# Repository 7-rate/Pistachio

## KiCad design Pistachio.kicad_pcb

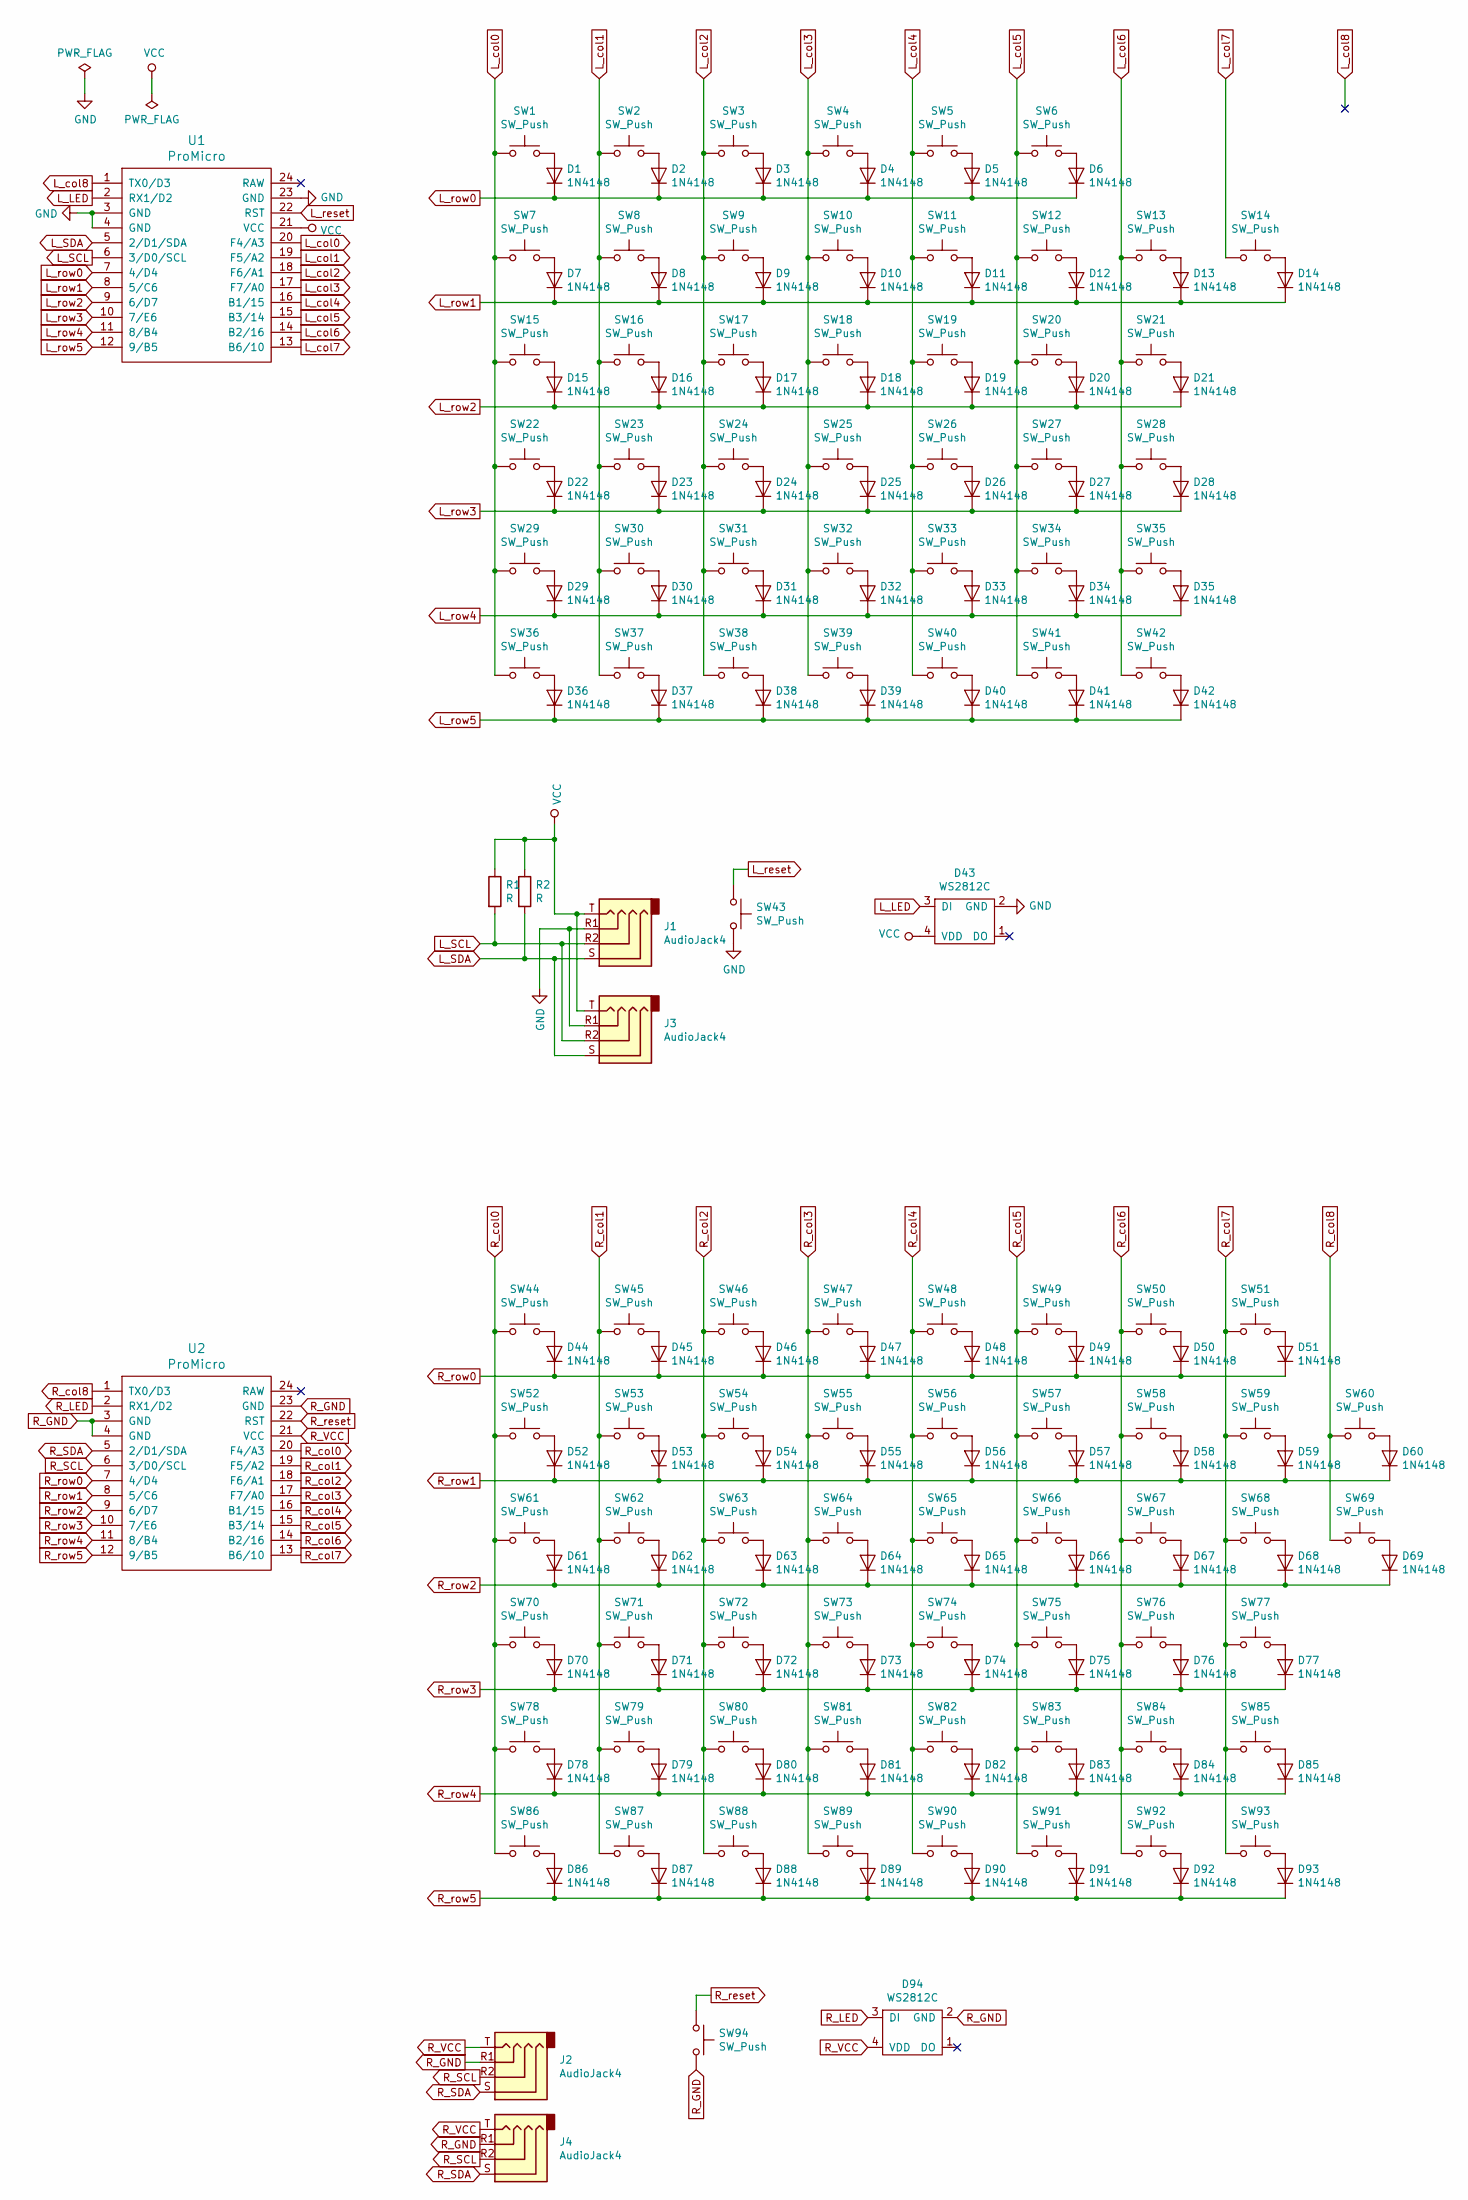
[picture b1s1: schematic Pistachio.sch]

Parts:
D1, D2, D3, D4, D5, D6, D7, D8, D9, D10, D11, D12, D13, D14, D15, D16, D17, D18, D19, D20, D21, D22, D23, D24, D25, D26, D27, D28, D29, D30, D31, D32, D33, D34, D35, D36, D37, D38, D39, D40, D41, D42, D44, D45, D46, D47, D48, D49, D50, D51, D52, D53, D54, D55, D56, D57, D58, D59, D60, D61, D62, D63, D64, D65, D66, D67, D68, D69, D70, D71, D72, D73, D74, D75, D76, D77, D78, D79, D80, D81, D82, D83, D84, D85, D86, D87, D88, D89, D90, D91, D92, D93: 1N4148; D3_SMD_v2
D43, D94: WS2812C; WS2812C-2020
J1, J2, J3, J4: AudioJack4; MJ-4PP-9_1side
R1, R2: R; R_0603_1608Metric_Pad1.05x0.95mm_HandSolder
SW1, SW2, SW3, SW4, SW5, SW6, SW7, SW8, SW9, SW10, SW11, SW12, SW13, SW14, SW15, SW16, SW17, SW18, SW19, SW20, SW21, SW22, SW23, SW24, SW25, SW26, SW27, SW28, SW29, SW30, SW31, SW32, SW33, SW34, SW35, SW36, SW37, SW38, SW39, SW40, SW41, SW42, SW44, SW45, SW46, SW47, SW48, SW49, SW50, SW51, SW52, SW53, SW54, SW55, SW56, SW57, SW58, SW59, SW60, SW61, SW62, SW63, SW64, SW65, SW66, SW67, SW68, SW69, SW70, SW71, SW72, SW73, SW74, SW75, SW76, SW77, SW78, SW79, SW80, SW81, SW82, SW83, SW84, SW85, SW86, SW87, SW88, SW89, SW90, SW91, SW92, SW93: SW_Push; Kailh_socket_MX_optional
SW43, SW94: SW_Push; ResetSW_1side
U1, U2: ProMicro; ProMicro_v3.5

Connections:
GND: D43.2 (GND), J1.R1, J3.R1, SW43.2, U1.3 (GND), U1.4 (GND), U1.23 (GND)
L_LED: D43.3 (DI), U1.2 (RX1/D2)
L_SCL: J1.R2, J3.R2, R1.2, U1.6 (3/D0/SCL)
L_SDA: J1.S, J3.S, R2.2, U1.5 (2/D1/SDA)
L_col0: SW1.1, SW7.1, SW15.1, SW22.1, SW29.1, SW36.1, U1.20 (F4/A3)
L_col1: SW2.1, SW8.1, SW16.1, SW23.1, SW30.1, SW37.1, U1.19 (F5/A2)
L_col2: SW3.1, SW9.1, SW17.1, SW24.1, SW31.1, SW38.1, U1.18 (F6/A1)
L_col3: SW4.1, SW10.1, SW18.1, SW25.1, SW32.1, SW39.1, U1.17 (F7/A0)
L_col4: SW5.1, SW11.1, SW19.1, SW26.1, SW33.1, SW40.1, U1.16 (B1/15)
L_col5: SW6.1, SW12.1, SW20.1, SW27.1, SW34.1, SW41.1, U1.15 (B3/14)
L_col6: SW13.1, SW21.1, SW28.1, SW35.1, SW42.1, U1.14 (B2/16)
L_col7: SW14.1, U1.13 (B6/10)
L_col8: U1.1 (TX0/D3)
L_reset: SW43.1, U1.22 (RST)
L_row0: D1.1 (K), D2.1 (K), D3.1 (K), D4.1 (K), D5.1 (K), D6.1 (K), U1.7 (4/D4)
L_row1: D7.1 (K), D8.1 (K), D9.1 (K), D10.1 (K), D11.1 (K), D12.1 (K), D13.1 (K), D14.1 (K), U1.8 (5/C6)
L_row2: D15.1 (K), D16.1 (K), D17.1 (K), D18.1 (K), D19.1 (K), D20.1 (K), D21.1 (K), U1.9 (6/D7)
L_row3: D22.1 (K), D23.1 (K), D24.1 (K), D25.1 (K), D26.1 (K), D27.1 (K), D28.1 (K), U1.10 (7/E6)
L_row4: D29.1 (K), D30.1 (K), D31.1 (K), D32.1 (K), D33.1 (K), D34.1 (K), D35.1 (K), U1.11 (8/B4)
L_row5: D36.1 (K), D37.1 (K), D38.1 (K), D39.1 (K), D40.1 (K), D41.1 (K), D42.1 (K), U1.12 (9/B5)
unnamed: D1.2 (A), SW1.2
unnamed: D2.2 (A), SW2.2
unnamed: D3.2 (A), SW3.2
unnamed: D4.2 (A), SW4.2
unnamed: D5.2 (A), SW5.2
unnamed: D6.2 (A), SW6.2
unnamed: D7.2 (A), SW7.2
unnamed: D8.2 (A), SW8.2
unnamed: D9.2 (A), SW9.2
unnamed: D10.2 (A), SW10.2
unnamed: D11.2 (A), SW11.2
unnamed: D12.2 (A), SW12.2
unnamed: D13.2 (A), SW13.2
unnamed: D14.2 (A), SW14.2
unnamed: D15.2 (A), SW15.2
unnamed: D16.2 (A), SW16.2
unnamed: D17.2 (A), SW17.2
unnamed: D18.2 (A), SW18.2
unnamed: D19.2 (A), SW19.2
unnamed: D20.2 (A), SW20.2
unnamed: D21.2 (A), SW21.2
unnamed: D22.2 (A), SW22.2
unnamed: D23.2 (A), SW23.2
unnamed: D24.2 (A), SW24.2
unnamed: D25.2 (A), SW25.2
unnamed: D26.2 (A), SW26.2
unnamed: D27.2 (A), SW27.2
unnamed: D28.2 (A), SW28.2
unnamed: D29.2 (A), SW29.2
unnamed: D30.2 (A), SW30.2
unnamed: D31.2 (A), SW31.2
unnamed: D32.2 (A), SW32.2
unnamed: D33.2 (A), SW33.2
unnamed: D34.2 (A), SW34.2
unnamed: D35.2 (A), SW35.2
unnamed: D36.2 (A), SW36.2
unnamed: D37.2 (A), SW37.2
unnamed: D38.2 (A), SW38.2
unnamed: D39.2 (A), SW39.2
unnamed: D40.2 (A), SW40.2
unnamed: D41.2 (A), SW41.2
unnamed: D42.2 (A), SW42.2
unnamed: D44.2 (A), SW44.2
unnamed: D45.2 (A), SW45.2
unnamed: D46.2 (A), SW46.2
unnamed: D47.2 (A), SW47.2
unnamed: D48.2 (A), SW48.2
unnamed: D49.2 (A), SW49.2
unnamed: D50.2 (A), SW50.2
unnamed: D51.2 (A), SW51.2
unnamed: D52.2 (A), SW52.2
unnamed: D53.2 (A), SW53.2
unnamed: D54.2 (A), SW54.2
unnamed: D55.2 (A), SW55.2
unnamed: D56.2 (A), SW56.2
unnamed: D57.2 (A), SW57.2
unnamed: D58.2 (A), SW58.2
unnamed: D59.2 (A), SW59.2
unnamed: D60.2 (A), SW60.2
unnamed: D61.2 (A), SW61.2
unnamed: D62.2 (A), SW62.2
unnamed: D63.2 (A), SW63.2
unnamed: D64.2 (A), SW64.2
unnamed: D65.2 (A), SW65.2
unnamed: D66.2 (A), SW66.2
unnamed: D67.2 (A), SW67.2
unnamed: D68.2 (A), SW68.2
unnamed: D69.2 (A), SW69.2
unnamed: D70.2 (A), SW70.2
unnamed: D71.2 (A), SW71.2
unnamed: D72.2 (A), SW72.2
unnamed: D73.2 (A), SW73.2
unnamed: D74.2 (A), SW74.2
unnamed: D75.2 (A), SW75.2
unnamed: D76.2 (A), SW76.2
unnamed: D77.2 (A), SW77.2
unnamed: D78.2 (A), SW78.2
unnamed: D79.2 (A), SW79.2
unnamed: D80.2 (A), SW80.2
unnamed: D81.2 (A), SW81.2
unnamed: D82.2 (A), SW82.2
unnamed: D83.2 (A), SW83.2
unnamed: D84.2 (A), SW84.2
unnamed: D85.2 (A), SW85.2
unnamed: D86.2 (A), SW86.2
unnamed: D87.2 (A), SW87.2
unnamed: D88.2 (A), SW88.2
unnamed: D89.2 (A), SW89.2
unnamed: D90.2 (A), SW90.2
unnamed: D91.2 (A), SW91.2
unnamed: D92.2 (A), SW92.2
unnamed: D93.2 (A), SW93.2
R_GND: D94.2 (GND), J2.R1, J4.R1, SW94.2, U2.3 (GND), U2.4 (GND), U2.23 (GND)
R_LED: D94.3 (DI), U2.2 (RX1/D2)
R_SCL: J2.R2, J4.R2, U2.6 (3/D0/SCL)
R_SDA: J2.S, J4.S, U2.5 (2/D1/SDA)
R_VCC: D94.4 (VDD), J2.T, J4.T, U2.21 (VCC)
R_col0: SW44.1, SW52.1, SW61.1, SW70.1, SW78.1, SW86.1, U2.20 (F4/A3)
R_col1: SW45.1, SW53.1, SW62.1, SW71.1, SW79.1, SW87.1, U2.19 (F5/A2)
R_col2: SW46.1, SW54.1, SW63.1, SW72.1, SW80.1, SW88.1, U2.18 (F6/A1)
R_col3: SW47.1, SW55.1, SW64.1, SW73.1, SW81.1, SW89.1, U2.17 (F7/A0)
R_col4: SW48.1, SW56.1, SW65.1, SW74.1, SW82.1, SW90.1, U2.16 (B1/15)
R_col5: SW49.1, SW57.1, SW66.1, SW75.1, SW83.1, SW91.1, U2.15 (B3/14)
R_col6: SW50.1, SW58.1, SW67.1, SW76.1, SW84.1, SW92.1, U2.14 (B2/16)
R_col7: SW51.1, SW59.1, SW68.1, SW77.1, SW85.1, SW93.1, U2.13 (B6/10)
R_col8: SW60.1, SW69.1, U2.1 (TX0/D3)
R_reset: SW94.1, U2.22 (RST)
R_row0: D44.1 (K), D45.1 (K), D46.1 (K), D47.1 (K), D48.1 (K), D49.1 (K), D50.1 (K), D51.1 (K), U2.7 (4/D4)
R_row1: D52.1 (K), D53.1 (K), D54.1 (K), D55.1 (K), D56.1 (K), D57.1 (K), D58.1 (K), D59.1 (K), D60.1 (K), U2.8 (5/C6)
R_row2: D61.1 (K), D62.1 (K), D63.1 (K), D64.1 (K), D65.1 (K), D66.1 (K), D67.1 (K), D68.1 (K), D69.1 (K), U2.9 (6/D7)
R_row3: D70.1 (K), D71.1 (K), D72.1 (K), D73.1 (K), D74.1 (K), D75.1 (K), D76.1 (K), D77.1 (K), U2.10 (7/E6)
R_row4: D78.1 (K), D79.1 (K), D80.1 (K), D81.1 (K), D82.1 (K), D83.1 (K), D84.1 (K), D85.1 (K), U2.11 (8/B4)
R_row5: D86.1 (K), D87.1 (K), D88.1 (K), D89.1 (K), D90.1 (K), D91.1 (K), D92.1 (K), D93.1 (K), U2.12 (9/B5)
VCC: D43.4 (VDD), J1.T, J3.T, R1.1, R2.1, U1.21 (VCC)

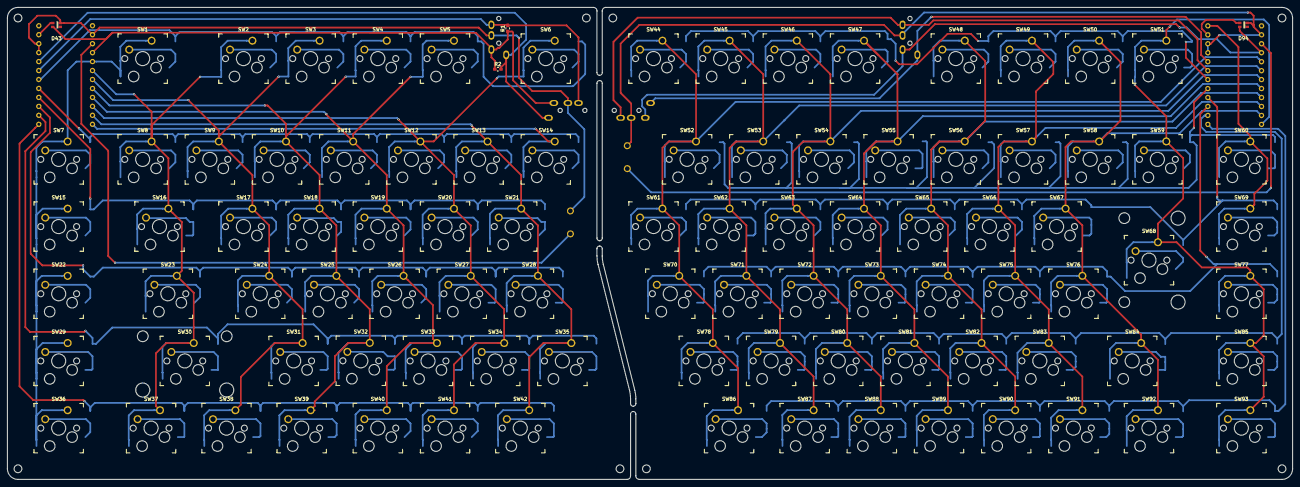
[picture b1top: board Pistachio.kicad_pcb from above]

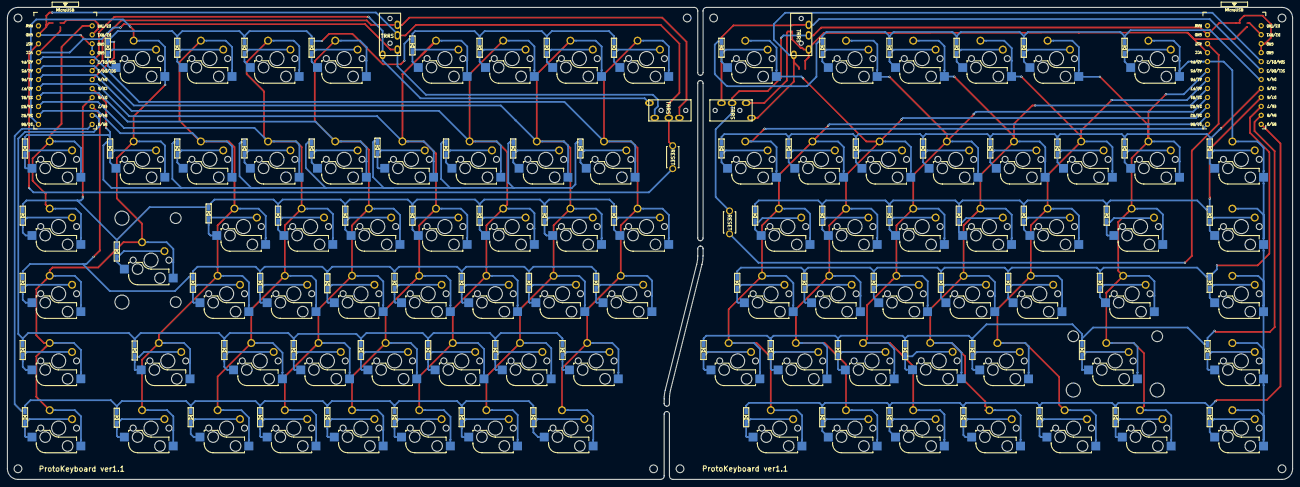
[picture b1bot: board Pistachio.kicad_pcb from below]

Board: 2 copper layers, 364.4 x 133.8 mm, 196 parts (100 on the bottom side), 133 nets.

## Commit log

2020-07-05 キー配置等の基本設計
2020-07-05 KiCADライブラリのサブモジュール追加
2020-07-11 サブモジュール削除
2020-07-11 サブモジュール追加
2020-07-12 ネッツリスト生成
2020-07-14 サブモジュール整理 一旦配線完了
2020-07-19 ベタGND、配線微調整、ロゴ追加
2020-08-03 左右統合版Keyboard Layout 追加
2020-08-21 qmk_configurator用、デフォルトキーマップ追加
2020-11-22 PDF回路図を追加
2021-04-25 ファイル構造整理
2021-05-25 Pistachio rev2
2021-05-30 Pistachio rev2.1
